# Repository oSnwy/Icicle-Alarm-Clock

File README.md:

# Icicle-Alarm-Clock

## Finished Build Images

|   </p> |   </p> |  </p> |
| - | - | - |

</p>

## Initial goals:
### Priority Goals:
- This alarm clock should be able to tell the time (obviously).
- This alarm clock should be able to store multiple alarms, as well as be able to toggle each alarm.
### Less important goals
- This alarm clock should have a volume knob.
- This alarm clock should be able to play customized sounds.

## Parts list (Bill of Materials)

| Part | Quantity | Price | Link |  
| ---------- | ---------- | ---------- | ---------- |
| Lolin C3 Mini ESP32 | 1 | Provided in Kit | N/A |
| 2.25in TFT display | 1 | Provided in Kit | N/A |
| Custom PCB | 1 | $8.67 | JLPCB |
| 3.3V Piezo Buzzer | 1 | Provided in Kit | N/A |
| EC11 Rotary Encoder Switch Button | 1 | $7.55 CAD | [AliExpress](https://www.aliexpress.com/item/1005008610645902.html?spm=a2g0o.productlist.main.4.2c317465sXCwvW&aem_p4p_detail=202607070924475087980507770000005617811&algo_pvid=e8d69d13-1db0-4bfd-9fc3-c2f3c209ff59&algo_exp_id=e8d69d13-1db0-4bfd-9fc3-c2f3c209ff59-3&pdp_ext_f=%7B%22order%22%3A%22342%22%2C%22eval%22%3A%221%22%2C%22fromPage%22%3A%22search%22%7D&pdp_npi=6%40dis%21CAD%214.48%214.47%21%21%213.08%213.07%21%402103123917834414872141769e2889%2112000045944331228%21sea%21CA%213742168056%21ABX%211%210%21n_tag%3A-29910%3Bd%3A5e0cbcd8%3Bm03_new_user%3A-29895%3BpisId%3A5000000206226397&curPageLogUid=CCZx2Qf1bu2y&utparam-url=scene%3Asearch%7Cquery_from%3A%7Cx_object_id%3A1005008610645902%7C_p_origin_prod%3A&search_p4p_id=202607070924475087980507770000005617811_1) |
| 1k ohm Resistor | 1 | $0.88 CAD | [AliExpress](https://www.aliexpress.com/item/1005007643210127.html?spm=a2g0o.productlist.main.2.6d624f792su7dm&algo_pvid=c0e45152-9ff0-4ec1-bf8a-26d206a77dc9&algo_exp_id=c0e45152-9ff0-4ec1-bf8a-26d206a77dc9-1&pdp_ext_f=%7B%22order%22%3A%22886%22%2C%22eval%22%3A%221%22%2C%22fromPage%22%3A%22search%22%7D&pdp_npi=6%40dis%21CAD%210.88%210.85%21%21%214.10%213.94%21%4021033d1217834393402286197efc5e%2112000041624997313%21sea%21CA%210%21ABX%211%210%21n_tag%3A-29910%3Bd%3A5e0cbcd8%3Bm03_new_user%3A-29895&curPageLogUid=x2mLNx3qELF5&utparam-url=scene%3Asearch%7Cquery_from%3A%7Cx_object_id%3A1005007643210127%7C_p_origin_prod%3A) |
| 10k Ohm Resistor | 1 | $0.88 CAD | [AliExpress](https://www.aliexpress.com/item/1005007643210127.html?spm=a2g0o.productlist.main.2.6d624f792su7dm&algo_pvid=c0e45152-9ff0-4ec1-bf8a-26d206a77dc9&algo_exp_id=c0e45152-9ff0-4ec1-bf8a-26d206a77dc9-1&pdp_ext_f=%7B%22order%22%3A%22886%22%2C%22eval%22%3A%221%22%2C%22fromPage%22%3A%22search%22%7D&pdp_npi=6%40dis%21CAD%210.88%210.85%21%21%214.10%213.94%21%4021033d1217834393402286197efc5e%2112000041624997313%21sea%21CA%210%21ABX%211%210%21n_tag%3A-29910%3Bd%3A5e0cbcd8%3Bm03_new_user%3A-29895&curPageLogUid=x2mLNx3qELF5&utparam-url=scene%3Asearch%7Cquery_from%3A%7Cx_object_id%3A1005007643210127%7C_p_origin_prod%3A) |
| S8050 Transistor | 1 | $7.47 CAD | [AliExpress](https://www.aliexpress.com/item/1005006811049225.html?spm=a2g0o.productlist.main.3.23a042ccHx9qk2&algo_pvid=fbd39ea5-1fc0-4b3e-8849-d372df714f92&algo_exp_id=fbd39ea5-1fc0-4b3e-8849-d372df714f92-2&pdp_ext_f=%7B%22order%22%3A%22191%22%2C%22spu_best_type%22%3A%22price%22%2C%22eval%22%3A%221%22%2C%22fromPage%22%3A%22search%22%7D&pdp_npi=6%40dis%21CAD%217.47%214.89%21%21%2134.89%2122.85%21%40210319b717834404073473874e8d99%2112000038384320363%21sea%21CA%210%21ABX%211%210%21n_tag%3A-29910%3Bd%3A5e0cbcd8%3Bm03_new_user%3A-29895&curPageLogUid=pNodTbyBBguG&utparam-url=scene%3Asearch%7Cquery_from%3A%7Cx_object_id%3A1005006811049225%7C_p_origin_prod%3A) |
| Case | 1 | Provided in Kit | N/A |
| Lid | 1 | Provided in Kit | N/A |
| 1x8 2.54mm pin headers | 2 | $3.72 CAD | [AliExpress](https://www.aliexpress.com/item/32847429443.html?spm=a2g0o.productlist.main.1.166537c1nJpVM4&algo_pvid=ee7e908c-bf01-4b82-bbfa-7b54397e240c&algo_exp_id=ee7e908c-bf01-4b82-bbfa-7b54397e240c-0&pdp_ext_f=%7B%22order%22%3A%22271%22%2C%22eval%22%3A%221%22%2C%22fromPage%22%3A%22search%22%7D&pdp_npi=6%40dis%21CAD%213.72%211.44%21%21%212.56%210.99%21%402103110517834417116324369e57b9%2165154055537%21sea%21CA%213742168056%21ABX%211%210%21n_tag%3A-29910%3Bd%3A5e0cbcd8%3Bm03_new_user%3A-29895%3BpisId%3A5000000207288090&curPageLogUid=epGjb5yLUGmR&utparam-url=scene%3Asearch%7Cquery_from%3A%7Cx_object_id%3A32847429443%7C_p_origin_prod%3A) |
| Keyboard Switches | 3 | Provided in Kit | N/A |
| Keyboard Keycaps | 3 | Provided in Kit | N/A |
| Male to male Dupont wires | 16 | $3.50 CAD | [AliExpress](https://www.aliexpress.com/item/4000109443054.html?spm=a2g0o.productlist.main.2.3b6b6071c6l0Fw&algo_pvid=0befaeab-1c07-467e-9051-386d31b85111&algo_exp_id=0befaeab-1c07-467e-9051-386d31b85111-1&pdp_ext_f=%7B%22order%22%3A%22203%22%2C%22eval%22%3A%221%22%2C%22fromPage%22%3A%22search%22%7D&pdp_npi=6%40dis%21CAD%213.50%211.44%21%21%212.41%210.99%21%402103122117834414202824009ecbf1%2110000000283106726%21sea%21CA%213742168056%21ABX%211%210%21n_tag%3A-29910%3Bd%3A5e0cbcd8%3Bm03_new_user%3A-29895%3BpisId%3A5000000210940427&curPageLogUid=BccdmUIZQV69&utparam-url=scene%3Asearch%7Cquery_from%3A%7Cx_object_id%3A4000109443054%7C_p_origin_prod%3A) | 

| Price | HST (Ontario Sales Tax) | Total Price | Total USD Price |  
| ---------- | ---------- | ---------- | ---------- |
| $32.67 CAD |  $4.25 CAD HST) | $36.92 CAD | 26.01 USD |

## Planning:
- I plan to use a rotary encoder with a switch to navigate the UI, as well as extra switches to toggle alarms or other features easily.
- The buzzer will be integrated into a transistor circuit, increasing the volume of the alarm while keeping it adjustable.

## Schemtaic (4 Hours):
- Due to the struggle for GPIO pins on the WEMOS, I was only able to add two switches.
- The rotary encoder and two switches use 5 GPIO pins, while the buzzer uses one.
- The THT display uses the other 6 GPIO pins.
- The 3.3V pin powers both the buzzer and the THT display.

## Schematic (REVISED: +2 Hours):
- While creating the PCB, I added a pull-down resistor between the base of the transistor circuit and the GND pin.
- I changed the THT display to be connected with a generic 2.54mm 1x8 connector, so the keys and screen can be mounted on separate planes.
- The BL is now powered by the 3.3V pin, freeing the GPIO pin to be used for a third switch.

## PCB (4 Hours)
- The PCB was wired in KiCad, using the footprints provided by Hack Club [BLARE](https://github.com/destroyer796/BLARE-Alarm-Clock/tree/main).
- All components were mounted on the top of the PCB.
- The PCB includes 4 mounting holes for M3 screws.
- This PCB uses a 1x8 connector for the display.

## Case (3 Hours)
This case is designed to work in two parts. The main body of the case has M3 screw standoffs in the base, allowing the PCB to be screwed into the case securely. The LCD can be attached to the front of the case using M2 screws in the hole in the front. The lid functions as a quick access to all the componenets inside, as well as contains a hole to reach the knob and switches. The side of the case contains cutouts to better transmit the sound of the buzzer.
- All 3d files can be found in the 3d model folder.
- The case and lid are stored in [/3d models/STEP files/Alarm Clock Base.step](https://github.com/oSnwy/Icicle-Alarm-Clock/blob/main/3d%20models/STEP%20files/Alarm%20Clock%20Base.step) and [/3d models/STEP files/Alarm Clock Lid.step](https://github.com/oSnwy/Icicle-Alarm-Clock/blob/main/3d%20models/STEP%20files/Alarm%20Clock%20Lid.step)

## CASE (REVISED: +2 Hours):
Added holes for the usb c wire, as well as a lower lid for easier access to the switches. Also added full electronics 3d model.

### Full Model With Electronics

|  |  |  |
|-|-|-|
|  |  |  |

### Case

|  |  |  |
|-|-|-|
|  |  |  |

### Lid

|  |  |  |
|-|-|-|
|  |  |  |

## Code (8 Hours)
Easily the longest part of the project. The code was written in C++ in the Arduino IDE. I used the wifi capabilities of the ESP32 to sync the time accurately without an RTC. This allows me to retrieve the time from pool.ntp.org, but does mean that it must be connected to the wifi. However, we can use the rotary encoder and the switches in order to mantually adjust the time if needed, such as when wifi is not possible.

### Resources Used
If anyone wants to learn how to code an Alarm Clock, these are some excellent resources to get started with.

| Use | Website |
| - | - |
| Install ESP32 in Arduino IDE | https://randomnerdtutorials.com/installing-the-esp32-board-in-arduino-ide-windows-instructions/ |
| How to connect ESP32 to wifi | https://randomnerdtutorials.com/getting-started-esp32-c3-super-mini/ |
| How to get the time on an ESP32 | https://randomnerdtutorials.com/esp32-date-time-ntp-client-server-arduino/ |
| struct TM reference sheet | https://cplusplus.com/reference/ctime/tm/ |
| WEMOS C3 mini reference sheet | https://www.wemos.cc/en/latest/c3/c3_mini.html |

Keep in mind that the type of microcontroller you are using may affect the firmware.

### Libraries
```C++
#include <Adafruit_GFX.h>
#include <Adafruit_ST7789.h>
#include <SPI.h>
#include <WiFi.h>
#include "time.h"
```
I used Adafruit and SPI to connect the microcontroller to the THT display, and wifi.h and time.h to get and store the time from pool.ntp.org. You may need to download the libraries before using them.

### Pins
```C++
#define BZ1 0
#define ENC_A 1
#define ENC_SW1 2
#define ENC_B 3
#define SW2 4
#define SW3 5
#define SW4 6
#define TFT_CS 7
#define TFT_DC 8
#define TFT_RST 10
#define TFT_MOSI 20
#define TFT_SCLK 21
```
Defining each pin of the microcontroller makes it easier and more organized. This will change depending on how your microcontroller is wired.

### Setting up Wifi and Time
```C++
const char* ssid = "wifi name";
const char* password = "wifi password";
const char* ntpServer = "pool.ntp.org";

const long gmtOffset_sec = -18000; // offset from gmt to test (-5 hours)
const int daylightOffset_sec = 3600; //off set froim daylight savings
```
We can access the wifi by using the ssid and password, which allows us to connect to the network later. The time can be found by getting the GMT timezone and offsetting it by the difference from GMT to EST, which is -5 hours. We can also use daylight savings offset to fix the hour difference.

### Display
```C++
Adafruit_ST7789 tft = Adafruit_ST7789(TFT_CS, TFT_DC, TFT_MOSI, TFT_SCLK, TFT_RST);
void setup() {
  Serial.begin(115200);a
  tft.init(284, 76);             
  tft.setColRowStart(82, 18);    
  tft.setRotation(2);            
  Serial.println("TFT Initialized!");

  tft.fillScreen(ST77XX_BLACK);  
  tft.setCursor(0, 0);           
  tft.setTextSize(2);          
  tft.print("Intializing");
}
```
This simply sets up the screen.

### Clock
```C++
int tries = 0;
  WiFi.begin(ssid, password);
  while (WiFi.status() != WL_CONNECTED && tries < 30) {
    delay(500);
    Serial.print(".");
    tries++;
  }
  
  configTime(gmtOffset_sec, daylightOffset_sec, ntpServer);

  if (getLocalTime(&timeinfo)) {
      Serial.println("Time synced!");
      showMessage("Time synced!");
      delay(1000);
    } else {
      Serial.println("Time sync failed!");
      showMessage("Time sync failed");
      delay(1500);
    }
  } else {
    Serial.println("\nWiFi failed!");
    showMessage("WiFi failed");
    delay(1500);
```
This block of code allows us to sync the internal clock of the microcontroller to the timezone, as well as any offsets.

### Alarm
```C++
void checkAlarm() { // check if its time to get up
  int hour, minute, second;

  if (!getCurrentTime(hour, minute, second)) {
    return;
  }

  // Reset the one-minute trigger lock when we leave the alarm minute.
  if (minute != alarmMinute) {
    alarmTriggeredThisMinute = false;
  }

  // If alarm is enabled and time matches, start ringing.
  if (
    alarmEnabled &&
    !alarmRinging &&
    !alarmTriggeredThisMinute &&
    hour == alarmHour &&
    minute == alarmMinute
  ) {
    alarmRinging = true;
    alarmTriggeredThisMinute = true;
  }
}

void updateBuzzer() { // if its time to get up gotta get the buzzer going
  if (!alarmRinging) {
    noTone(BZ1);
    beepOn = false;
    return;
  }

  // Make the alarm beep on/off every 300 ms.
  if (millis() - lastBeepToggle > 300) {
    lastBeepToggle = millis();
    beepOn = !beepOn;

    if (beepOn) {
      tone(BZ1, 2000);   // 2000 Hz beep
    } else {
      noTone(BZ1);
    }
  }
}
```
We can use a function in order to check whether the alarm should be going off. The updateBuzzer function allows us to make the buzzer beep on and off, as well as test when it should be stopped.

### Clock Adjustment
```C++
void changeValue(int amount) { 
  if (mode == SET_ALARM_MINUTE) {
      alarmMinute += amount;
  if (mode == SET_ALARM_HOUR) {
      alarmHour += amount;
}
```
We can use the rotary knob and switches in tandem to adjust the clock's time in case of desync.
```C++
// SW2 can set hour time
  if (buttonPressed(sw2State, lastSW2)) {
    mode = SET_ALARM_HOUR;
    lastButtonTime = millis();
  }

  // SW3 toggles alarm on/off
  if (buttonPressed(sw3State, lastSW3)) {
    alarmEnabled = !alarmEnabled;
    mode = SHOW_TIME;
    lastButtonTime = millis();
  }

  // SW4 goes back to main screen
  if (buttonPressed(sw4State, lastSW4)) {
    mode = SHOW_TIME;
    lastButtonTime = millis();
  }

  // Rotary encoder switch moves between setting hour and minute
  if (buttonPressed(encSWState, lastEncSW)) {
    if (mode == SHOW_TIME) {
      mode = SET_ALARM_HOUR;
    } else if (mode == SET_ALARM_HOUR) {
      mode = SET_ALARM_MINUTE;
    } else if (mode == SET_ALARM_MINUTE) {
      mode = SHOW_TIME;
    }
```
The detection of the switches and rotary encoder allows us to change the UI and set the alarm and clock.

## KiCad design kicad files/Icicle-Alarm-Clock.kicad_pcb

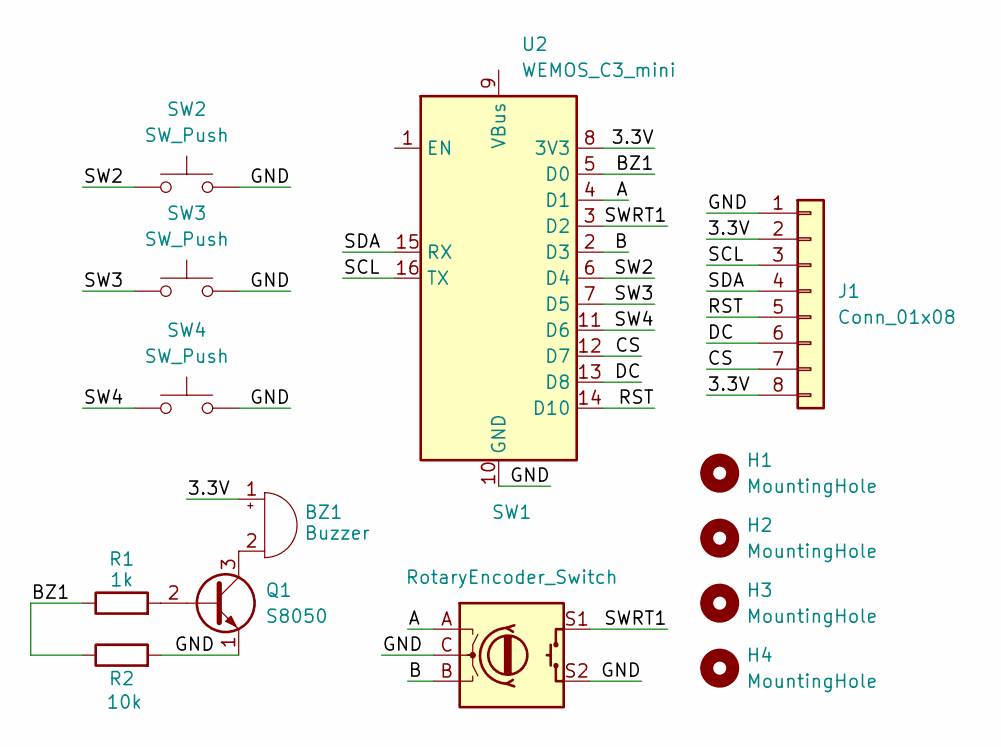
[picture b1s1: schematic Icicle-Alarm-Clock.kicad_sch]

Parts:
BZ1: Buzzer; Buzzer_12x9.5RM7.6
H1, H2, H3, H4: MountingHole; MountingHole_3.2mm_M3
J1: Conn_01x08; PinHeader_1x08_P2.54mm_Vertical
Q1: S8050; TO-92_Inline
R1: 1k; R_Axial_DIN0207_L6.3mm_D2.5mm_P7.62mm_Horizontal
R2: 10k; R_Axial_DIN0207_L6.3mm_D2.5mm_P7.62mm_Horizontal
SW1: RotaryEncoder_Switch; RotaryEncoder_Alps_EC11E-Switch_Vertical_H20mm
SW2, SW3, SW4: SW_Push; SW_MX_1u
U2: WEMOS_C3_mini

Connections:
/3.3V: BZ1.1 (+), J1.2, J1.8, U2.8 (3V3)
/A: SW1.A, U2.4 (D1)
/B: SW1.B, U2.2 (D3)
/BZ1: R1.1, R2.1, U2.5 (D0)
/CS: J1.7, U2.12 (D7)
/DC: J1.6, U2.13 (D8)
/GND: J1.1, Q1.1 (E), R2.2, SW1.C, SW1.S2, SW2.2, SW3.2, SW4.2, U2.10 (GND)
/RST: J1.5, U2.14 (D10)
/SCL: J1.3, U2.16 (TX)
/SDA: J1.4, U2.15 (RX)
/SW2: SW2.1, U2.6 (D4)
/SW3: SW3.1, U2.7 (D5)
/SW4: SW4.1, U2.11 (D6)
/SWRT1: SW1.S1, U2.3 (D2)
unnamed: BZ1.2 (-), Q1.3 (C)
unnamed: Q1.2 (B), R1.2

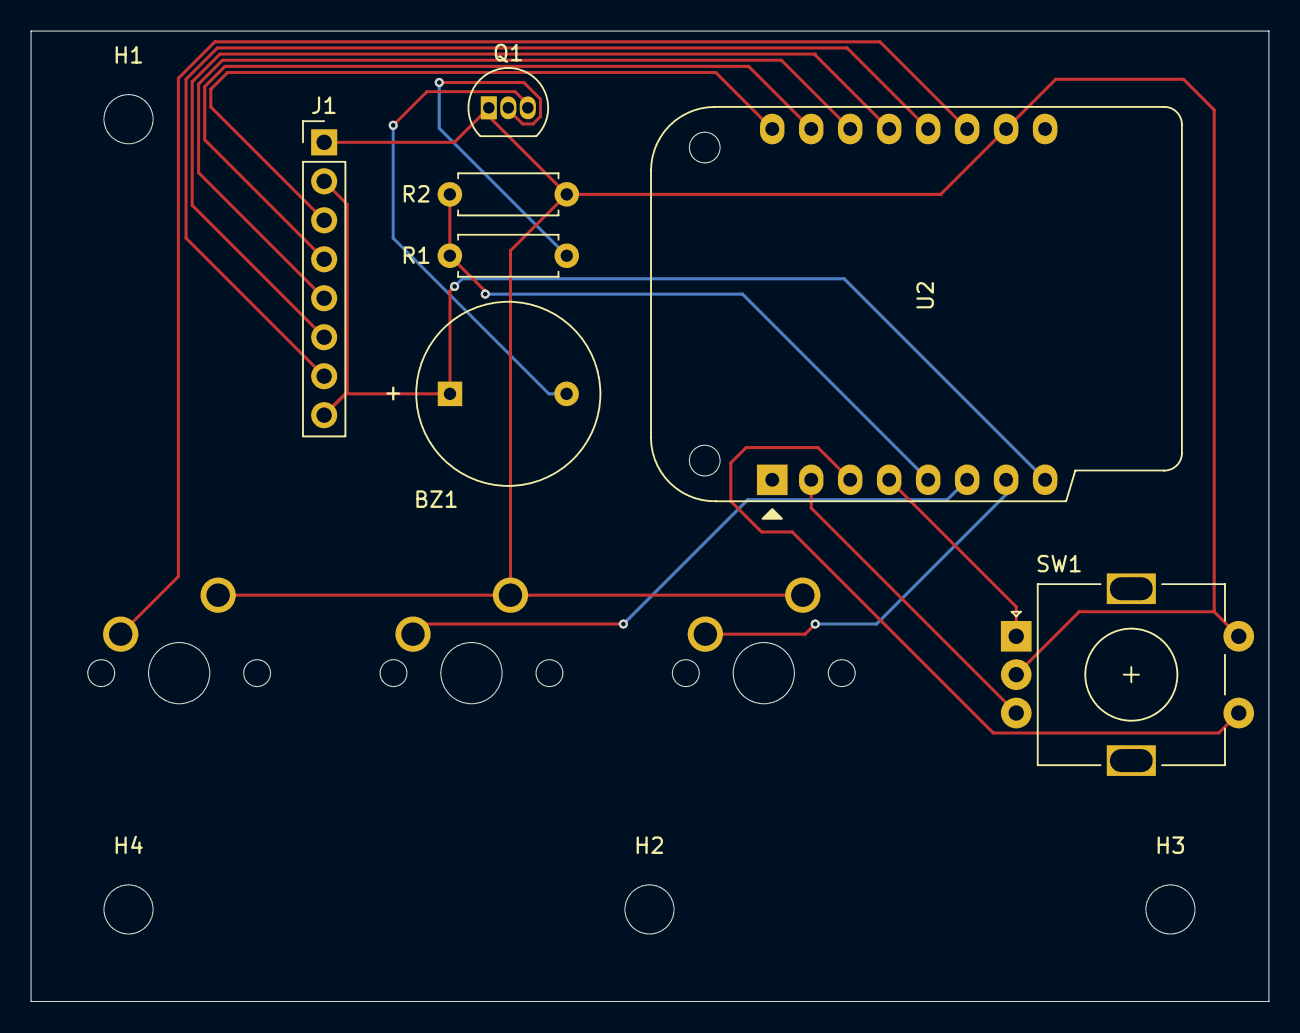
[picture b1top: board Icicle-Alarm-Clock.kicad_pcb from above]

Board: 2 copper layers, 80.7 x 63.2 mm, 14 parts (0 on the bottom side), 16 nets.
